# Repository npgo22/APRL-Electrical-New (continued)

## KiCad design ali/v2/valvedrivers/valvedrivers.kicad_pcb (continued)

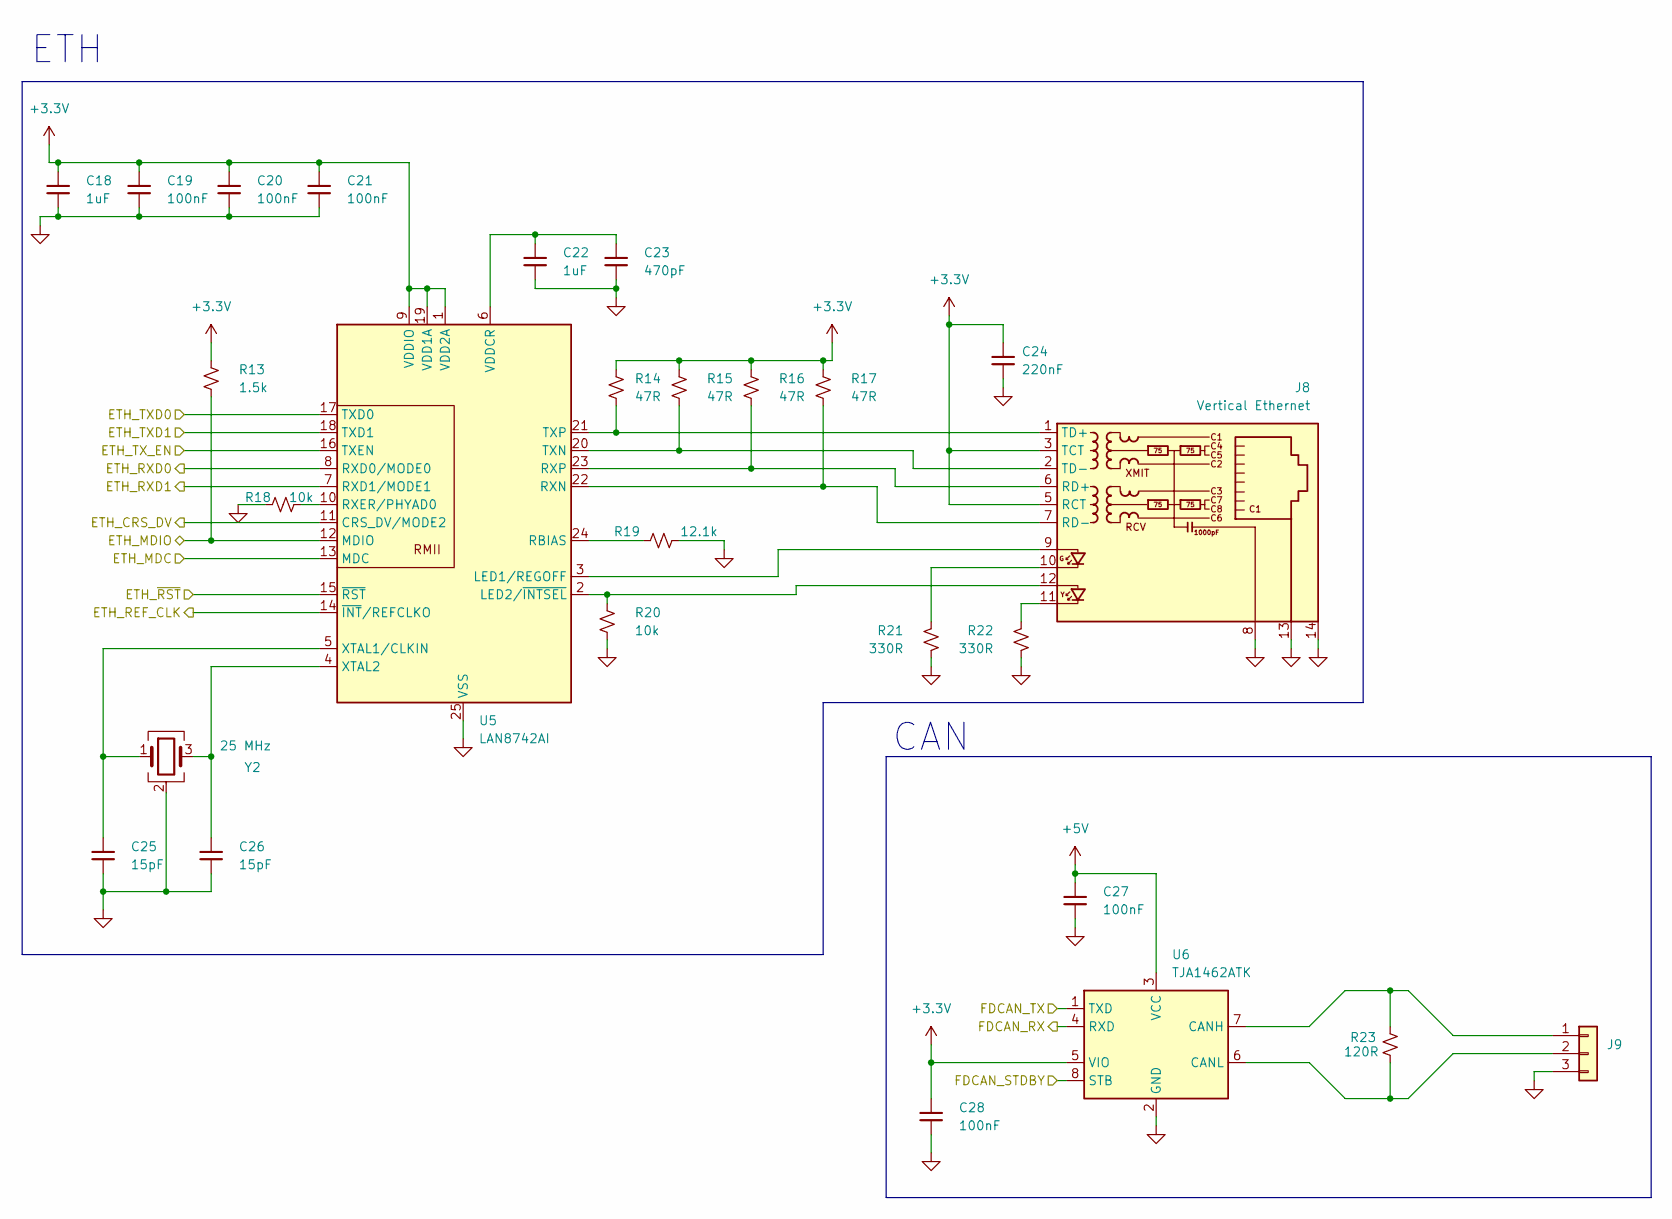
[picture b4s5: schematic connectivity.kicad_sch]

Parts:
C18, C22: 1uF; C_0603; MPN GRM188D72A105KE01
C19, C20, C21, C27, C28: 100nF; C_0603; MPN GRM188R72A104KA35
C23: 470pF; C_0603; MPN GRM1885C1H471JA01
C24: 220nF; C_0603; MPN GRM188R71H224KAC4
C25, C26: 15pF; C_0603; MPN GRM1885C2E150FW07
J8: Vertical Ethernet; RJ45_Hanrun_HY951180A_Vertical; MPN HY951180A
J9: Conn_01x03; Molex_CLIK-Mate_503159-0301_1x03-1MP_P1.50mm_Vertical; MPN 503159-0301
R13: 1.5k; R_0603; MPN RC0603FR-071K5L
R14, R15, R16, R17: 47R; R_0603; MPN RC0603FR-0747RL
R18, R20: 10k; R_0603; MPN RC0603FR-0710KL
R19: 12.1k; R_0603; MPN RT0603BRD0712K1L
R21, R22: 330R; R_0603; MPN RC0603FR-07330RL
R23: 120R; R_0603; MPN AC0603FR-07120RL
U5: LAN8742AI; VQFN-24-1EP_4x4mm_P0.5mm_EP2.5x2.5mm_ThermalVias; MPN LAN8742AI-CZ-TR
U6: TJA1462ATK; HVSON-8-1EP_3x3mm_P0.65mm_EP1.6x2.4mm_ThermalVias; MPN TJA1462ATK/0Z
Y2: 25 MHz; 3225-4P-L; MPN X1E0000210139

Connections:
+3.3V: C18.1, C19.1, C20.1, C21.1, C24.1, C28.1, J8.3 (TCT), J8.5 (RCT), R13.1, R14.1, R15.1, R16.1, R17.1, U5.1 (VDD2A), U5.9 (VDDIO), U5.19 (VDD1A), U6.5 (VIO); also elsewhere on the board
+5V: C27.1, U6.3 (VCC); also elsewhere on the board
/Connectivity/ETH_CRS_DV: U5.11 (CRS_DV/MODE2); also elsewhere on the board
/Connectivity/ETH_MDC: U5.13 (MDC); also elsewhere on the board
/Connectivity/ETH_MDIO: R13.2, U5.12 (MDIO); also elsewhere on the board
/Connectivity/ETH_REF_CLK: U5.14 (~INT/REFCLKO); also elsewhere on the board
/Connectivity/ETH_RXD0: U5.8 (RXD0/MODE0); also elsewhere on the board
/Connectivity/ETH_RXD1: U5.7 (RXD1/MODE1); also elsewhere on the board
/Connectivity/ETH_TXD0: U5.17 (TXD0); also elsewhere on the board
/Connectivity/ETH_TXD1: U5.18 (TXD1); also elsewhere on the board
/Connectivity/ETH_TX_EN: U5.16 (TXEN); also elsewhere on the board
/Connectivity/ETH_~RST: U5.15 (~RST); also elsewhere on the board
/Connectivity/FDCAN_RX: U6.4 (RXD); also elsewhere on the board
/Connectivity/FDCAN_STDBY: U6.8 (STB); also elsewhere on the board
/Connectivity/FDCAN_TX: U6.1 (TXD); also elsewhere on the board
GND: C18.2, C19.2, C20.2, C21.2, C22.2, C23.2, C24.2, C25.2, C26.2, C27.2, C28.2, J8.8, J8.13, J8.14, J9.3, R18.1, R19.2, R20.2, R21.2, R22.2, U5.25 (VSS), U6.2 (GND), U6.9 (GND), Y2.2 (G), Y2.4 (G); also elsewhere on the board
unnamed: J8.10, R21.1
unnamed: J8.11, R22.1
unnamed: J8.6 (RD+), R16.2, U5.23 (RXP)
unnamed: J8.7 (RD-), R17.2, U5.22 (RXN)
unnamed: J8.1 (TD+), R14.2, U5.21 (TXP)
unnamed: J8.2 (TD-), R15.2, U5.20 (TXN)
unnamed: J9.1, R23.2, U6.7 (CANH)
unnamed: J9.2, R23.1, U6.6 (CANL)
unnamed: J8.9, U5.3 (LED1/REGOFF)
unnamed: J8.12, R20.1, U5.2 (LED2/~INTSEL)
unnamed: R19.1, U5.24 (RBIAS)
unnamed: R18.2, U5.10 (RXER/PHYAD0)
unnamed: C22.1, C23.1, U5.6 (VDDCR)
unnamed: C25.1, U5.5 (XTAL1/CLKIN), Y2.1
unnamed: C26.1, U5.4 (XTAL2), Y2.3

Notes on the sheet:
ETH
CAN

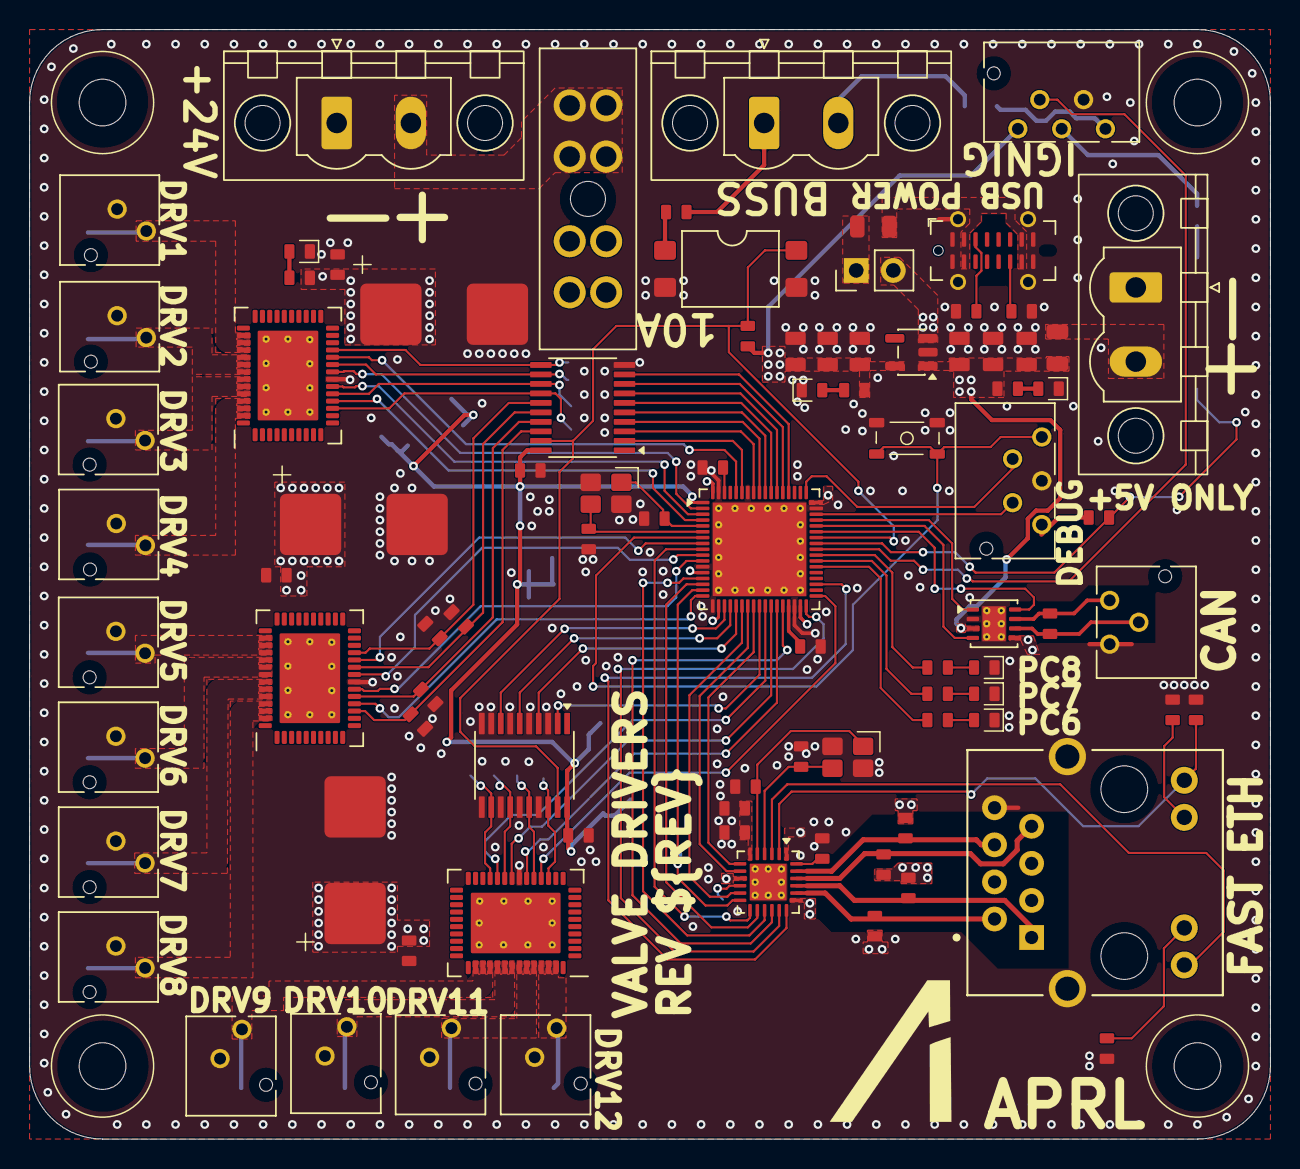
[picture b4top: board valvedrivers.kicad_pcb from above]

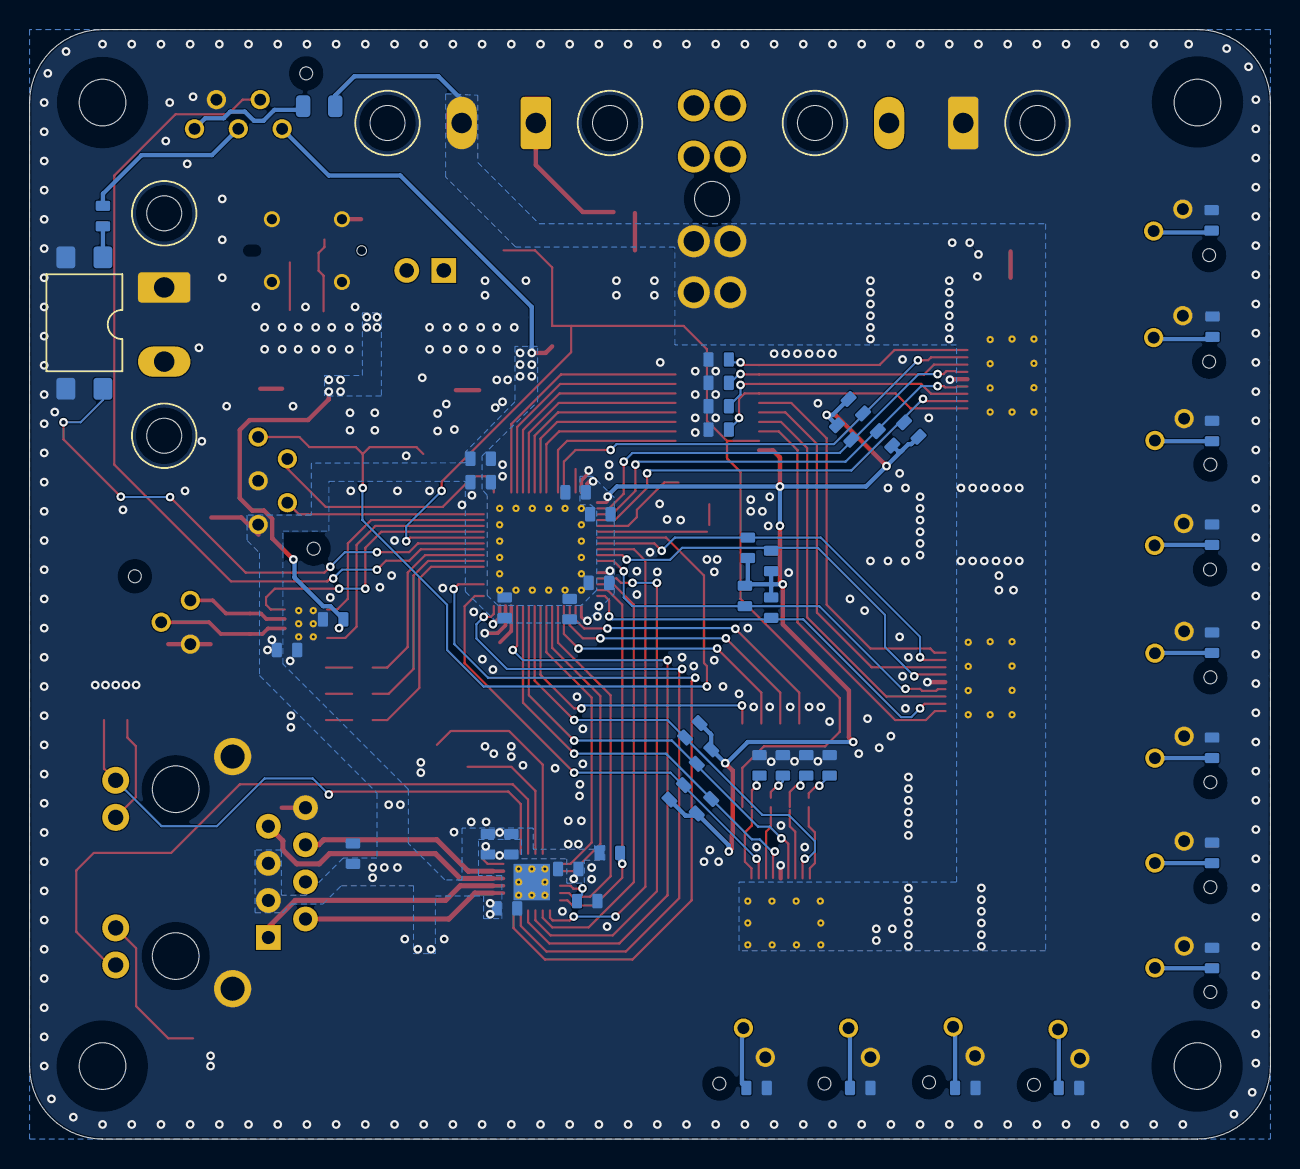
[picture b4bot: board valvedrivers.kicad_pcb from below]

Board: 4 copper layers, 85.0 x 76.0 mm, 144 parts (51 on the bottom side), 110 nets.

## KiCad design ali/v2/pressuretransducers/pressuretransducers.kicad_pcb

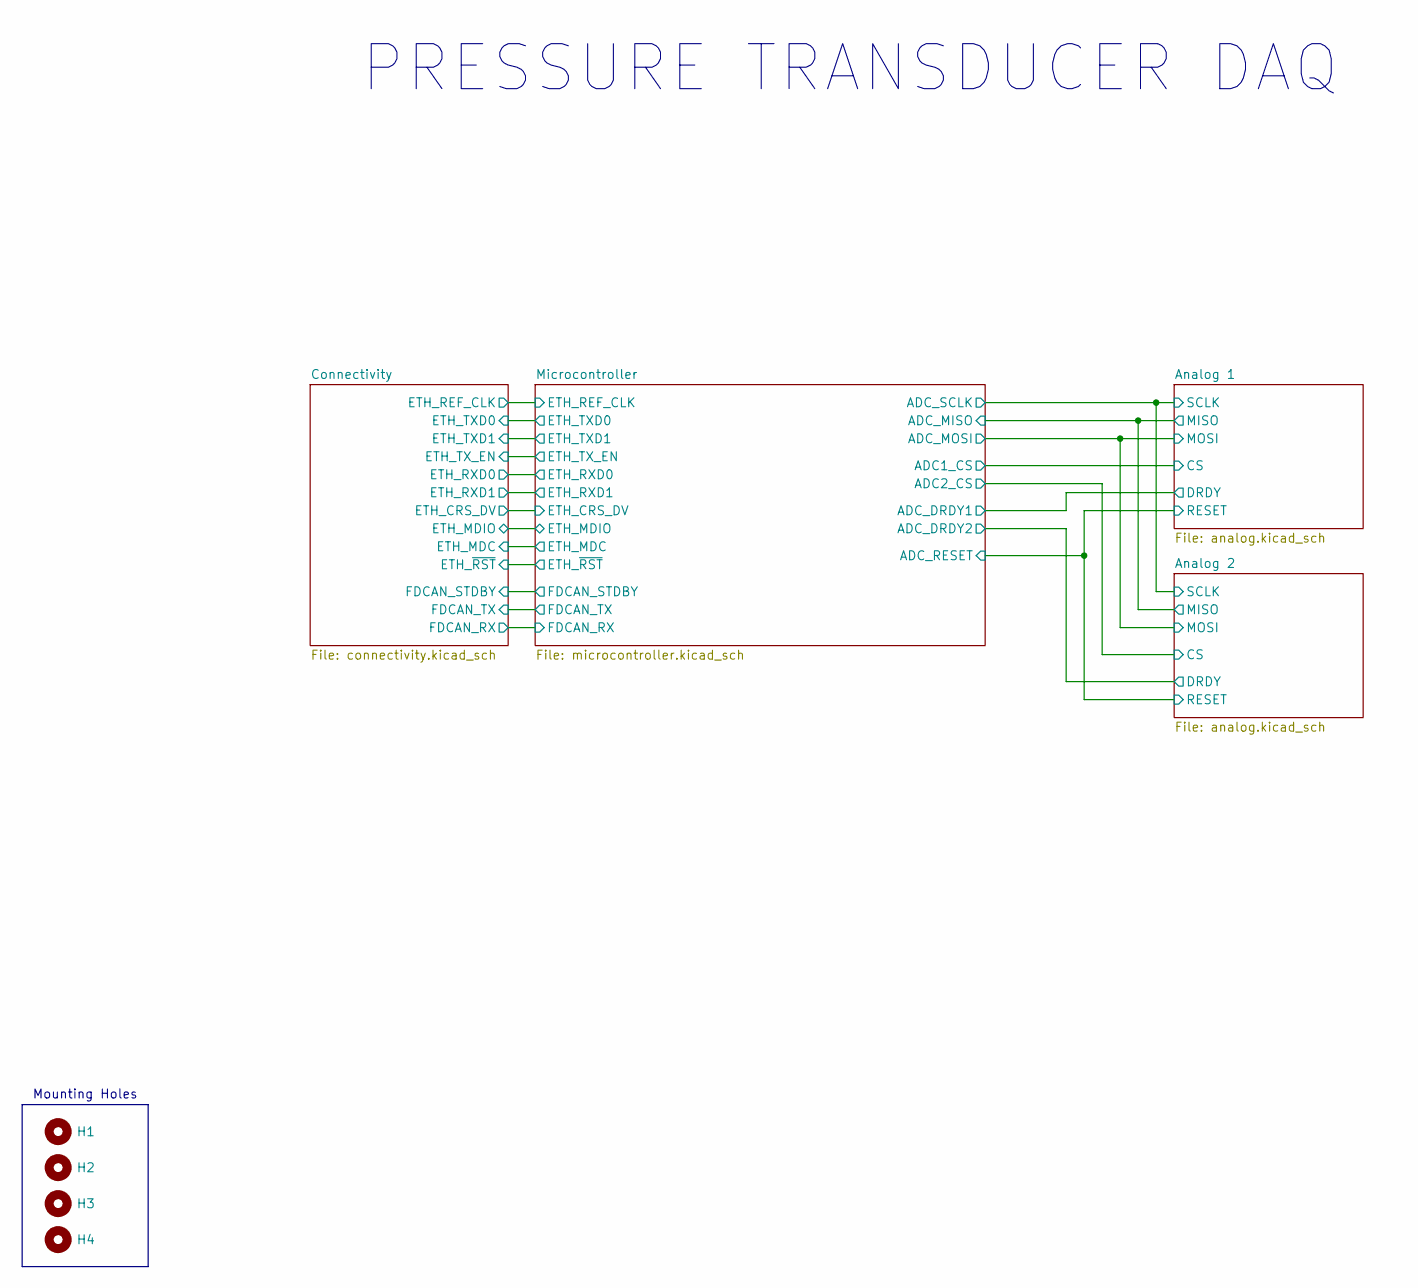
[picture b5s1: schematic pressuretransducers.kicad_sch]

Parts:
H1, H2, H3, H4: MountingHole; MountingHole_3.2mm_M3

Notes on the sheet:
PRESSURE TRANSDUCER DAQ
Mounting Holes

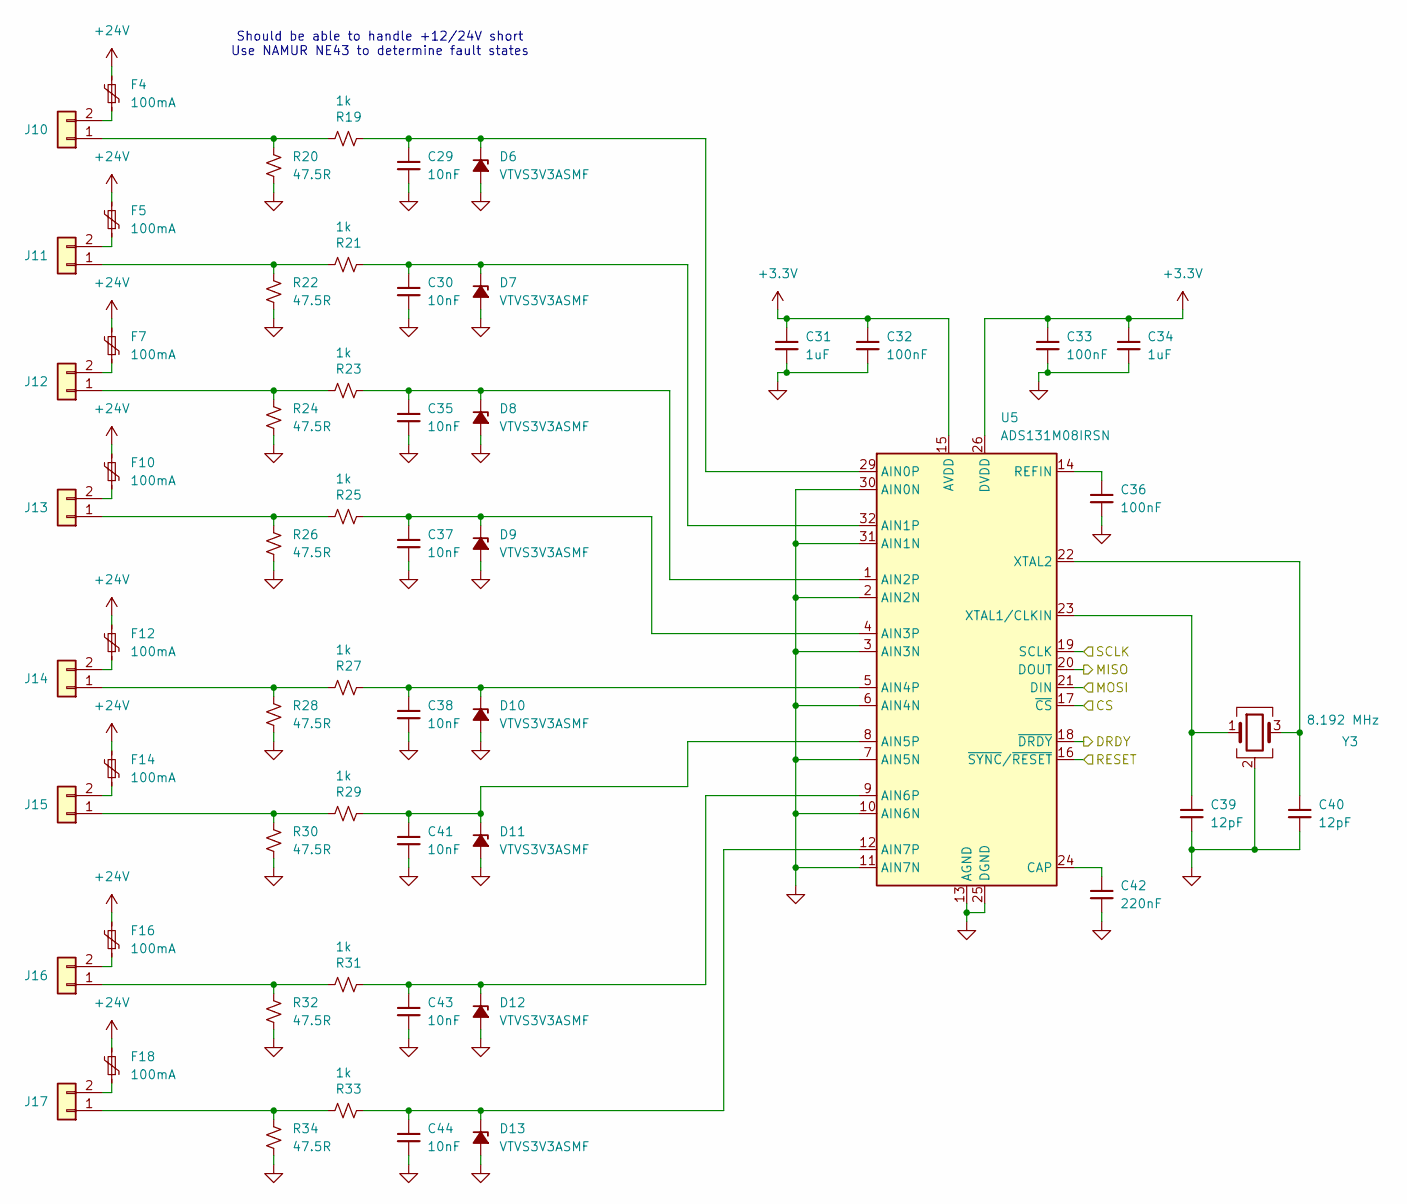
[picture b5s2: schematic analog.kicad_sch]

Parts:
C29, C30, C35, C37, C38, C41, C43, C44: 10nF; C_0603; MPN GRM1885C1H103JA01
C31, C34: 1uF; C_0603; MPN GRM188D72A105KE01
C32, C33, C36: 100nF; C_0603; MPN GRM188R72A104KA35
C39, C40: 12pF; C_0603; MPN C0603C120J5GACTU
C42: 220nF; C_0603; MPN GRM188R71H224KAC4
D6, D7, D8, D9, D10, D11, D12, D13: VTVS3V3ASMF; D_SMF; MPN VTVS3V3ASMF-M3-08
F4, F5, F7, F10, F12, F14, F16, F18: 100mA; Fuse_1206_3216Metric; MPN 1206L010/60WR
J10, J11, J12, J13, J14, J15, J16, J17: Conn_01x02; Molex_CLIK-Mate_503159-0201_1x02-1MP_P1.50mm_Vertical; MPN 503159-0201
R19, R21, R23, R25, R27, R29, R31, R33: 1k; R_0603; MPN RT0603BRD071KL
R20, R22, R24, R26, R28, R30, R32, R34: 47.5R; R_0805; MPN ERA-6AEB47R5V
U5: ADS131M08IRSN; QFN-32_EP_4.4x4.4_Pitch0.4mm; MPN ADS131M08IRSNR
Y3: 8.192 MHz; 3225-4P-L; MPN 7B008192I01

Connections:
+3.3V: C31.1, C32.1, C33.1, C34.1, U5.15 (AVDD), U5.26 (DVDD); also elsewhere on the board
+24V: F4.2, F5.2, F7.2, F10.2, F12.2, F14.2, F16.2, F18.2; also elsewhere on the board
/Analog 1/CS: U5.17 (~CS); also elsewhere on the board
/Analog 1/DRDY: U5.18 (~DRDY); also elsewhere on the board
/Analog 1/MISO: U5.20 (DOUT); also elsewhere on the board
/Analog 1/MOSI: U5.21 (DIN); also elsewhere on the board
/Analog 1/RESET: U5.16 (~SYNC/~RESET); also elsewhere on the board
/Analog 1/SCLK: U5.19 (SCLK); also elsewhere on the board
GND: C29.1, C30.1, C31.2, C32.2, C33.2, C34.2, C35.1, C36.2, C37.1, C38.1, C39.2, C40.2, C41.1, C42.2, C43.1, C44.1, D6.2 (A), D7.2 (A), D8.2 (A), D9.2 (A), D10.2 (A), D11.2 (A), D12.2 (A), D13.2 (A), R20.2, R22.2, R24.2, R26.2, R28.2, R30.2, R32.2, R34.2, U5.2 (AIN2N), U5.3 (AIN3N), U5.6 (AIN4N), U5.7 (AIN5N), U5.10 (AIN6N), U5.11 (AIN7N), U5.13 (AGND), U5.25 (DGND), U5.27 (AGND), U5.28 (AGND), U5.30 (AIN0N), U5.31 (AIN1N), U5.33 (GND), Y3.2 (G), Y3.4 (G); also elsewhere on the board
unnamed: C29.2, D6.1 (K), R19.2, U5.29 (AIN0P)
unnamed: C30.2, D7.1 (K), R21.2, U5.32 (AIN1P)
unnamed: C35.2, D8.1 (K), R23.2, U5.1 (AIN2P)
unnamed: C37.2, D9.1 (K), R25.2, U5.4 (AIN3P)
unnamed: C38.2, D10.1 (K), R27.2, U5.5 (AIN4P)
unnamed: C41.2, D11.1 (K), R29.2, U5.8 (AIN5P)
unnamed: C43.2, D12.1 (K), R31.2, U5.9 (AIN6P)
unnamed: C44.2, D13.1 (K), R33.2, U5.12 (AIN7P)
unnamed: J10.1, R19.1, R20.1
unnamed: F4.1, J10.2
unnamed: J11.1, R21.1, R22.1
unnamed: F5.1, J11.2
unnamed: J12.1, R23.1, R24.1
unnamed: F7.1, J12.2
unnamed: J13.1, R25.1, R26.1
unnamed: F10.1, J13.2
unnamed: J14.1, R27.1, R28.1
unnamed: F12.1, J14.2
unnamed: J15.1, R29.1, R30.1
unnamed: F14.1, J15.2
unnamed: J16.1, R31.1, R32.1
unnamed: F16.1, J16.2
unnamed: J17.1, R33.1, R34.1
unnamed: F18.1, J17.2
unnamed: C42.1, U5.24 (CAP)
unnamed: C36.1, U5.14 (REFIN)
unnamed: C39.1, U5.23 (XTAL1/CLKIN), Y3.1
unnamed: C40.1, U5.22 (XTAL2), Y3.3

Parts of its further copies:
C45, C46, C51, C53, C54, C57, C59, C60: 10nF; C_0603; MPN GRM1885C1H103JA01
C47, C50: 1uF; C_0603; MPN GRM188D72A105KE01
C48, C49, C52: 100nF; C_0603; MPN GRM188R72A104KA35
C55, C56: 12pF; C_0603; MPN C0603C120J5GACTU
C58: 220nF; C_0603; MPN GRM188R71H224KAC4
D14, D15, D16, D17, D18, D19, D20, D21: VTVS3V3ASMF; D_SMF; MPN VTVS3V3ASMF-M3-08
F6, F8, F9, F11, F13, F15, F17, F19: 100mA; Fuse_1206_3216Metric; MPN 1206L010/60WR
J18, J19, J20, J21, J22, J23, J24, J25: Conn_01x02; Molex_CLIK-Mate_503159-0201_1x02-1MP_P1.50mm_Vertical; MPN 503159-0201
R35, R37, R39, R41, R43, R45, R47, R49: 1k; R_0603; MPN RT0603BRD071KL
R36, R38, R40, R42, R44, R46, R48, R50: 47.5R; R_0805; MPN ERA-6AEB47R5V
U6: ADS131M08IRSN; QFN-32_EP_4.4x4.4_Pitch0.4mm; MPN ADS131M08IRSNR
Y4: 8.192 MHz; 3225-4P-L; MPN 7B008192I01

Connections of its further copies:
+3.3V: C47.1, C48.1, C49.1, C50.1, U6.15 (AVDD), U6.26 (DVDD); also elsewhere on the board
+24V: F6.2, F8.2, F9.2, F11.2, F13.2, F15.2, F17.2, F19.2; also elsewhere on the board
/Analog 1/MISO: U6.20 (DOUT); also elsewhere on the board
/Analog 1/MOSI: U6.21 (DIN); also elsewhere on the board
/Analog 1/RESET: U6.16 (~SYNC/~RESET); also elsewhere on the board
/Analog 1/SCLK: U6.19 (SCLK); also elsewhere on the board
/Analog 2/CS: U6.17 (~CS); also elsewhere on the board
/Analog 2/DRDY: U6.18 (~DRDY); also elsewhere on the board
GND: C45.1, C46.1, C47.2, C48.2, C49.2, C50.2, C51.1, C52.2, C53.1, C54.1, C55.2, C56.2, C57.1, C58.2, C59.1, C60.1, D14.2 (A), D15.2 (A), D16.2 (A), D17.2 (A), D18.2 (A), D19.2 (A), D20.2 (A), D21.2 (A), R36.2, R38.2, R40.2, R42.2, R44.2, R46.2, R48.2, R50.2, U6.2 (AIN2N), U6.3 (AIN3N), U6.6 (AIN4N), U6.7 (AIN5N), U6.10 (AIN6N), U6.11 (AIN7N), U6.13 (AGND), U6.25 (DGND), U6.27 (AGND), U6.28 (AGND), U6.30 (AIN0N), U6.31 (AIN1N), U6.33 (GND), Y4.2 (G), Y4.4 (G); also elsewhere on the board
unnamed: C45.2, D14.1 (K), R35.2, U6.29 (AIN0P)
unnamed: C46.2, D15.1 (K), R37.2, U6.32 (AIN1P)
unnamed: C51.2, D16.1 (K), R39.2, U6.1 (AIN2P)
unnamed: C53.2, D17.1 (K), R41.2, U6.4 (AIN3P)
unnamed: C54.2, D18.1 (K), R43.2, U6.5 (AIN4P)
unnamed: C57.2, D19.1 (K), R45.2, U6.8 (AIN5P)
unnamed: C59.2, D20.1 (K), R47.2, U6.9 (AIN6P)
unnamed: C60.2, D21.1 (K), R49.2, U6.12 (AIN7P)
unnamed: J18.1, R35.1, R36.1
unnamed: F8.1, J18.2
unnamed: J19.1, R37.1, R38.1
unnamed: F6.1, J19.2
unnamed: J20.1, R39.1, R40.1
unnamed: F9.1, J20.2
unnamed: J21.1, R41.1, R42.1
unnamed: F11.1, J21.2
unnamed: J22.1, R43.1, R44.1
unnamed: F13.1, J22.2
unnamed: J23.1, R45.1, R46.1
unnamed: F15.1, J23.2
unnamed: J24.1, R47.1, R48.1
unnamed: F17.1, J24.2
unnamed: J25.1, R49.1, R50.1
unnamed: F19.1, J25.2
unnamed: C58.1, U6.24 (CAP)
unnamed: C52.1, U6.14 (REFIN)
unnamed: C55.1, U6.23 (XTAL1/CLKIN), Y4.1
unnamed: C56.1, U6.22 (XTAL2), Y4.3

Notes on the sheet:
Should be able to handle +12/24V short Use NAMUR NE43 to determine fault states

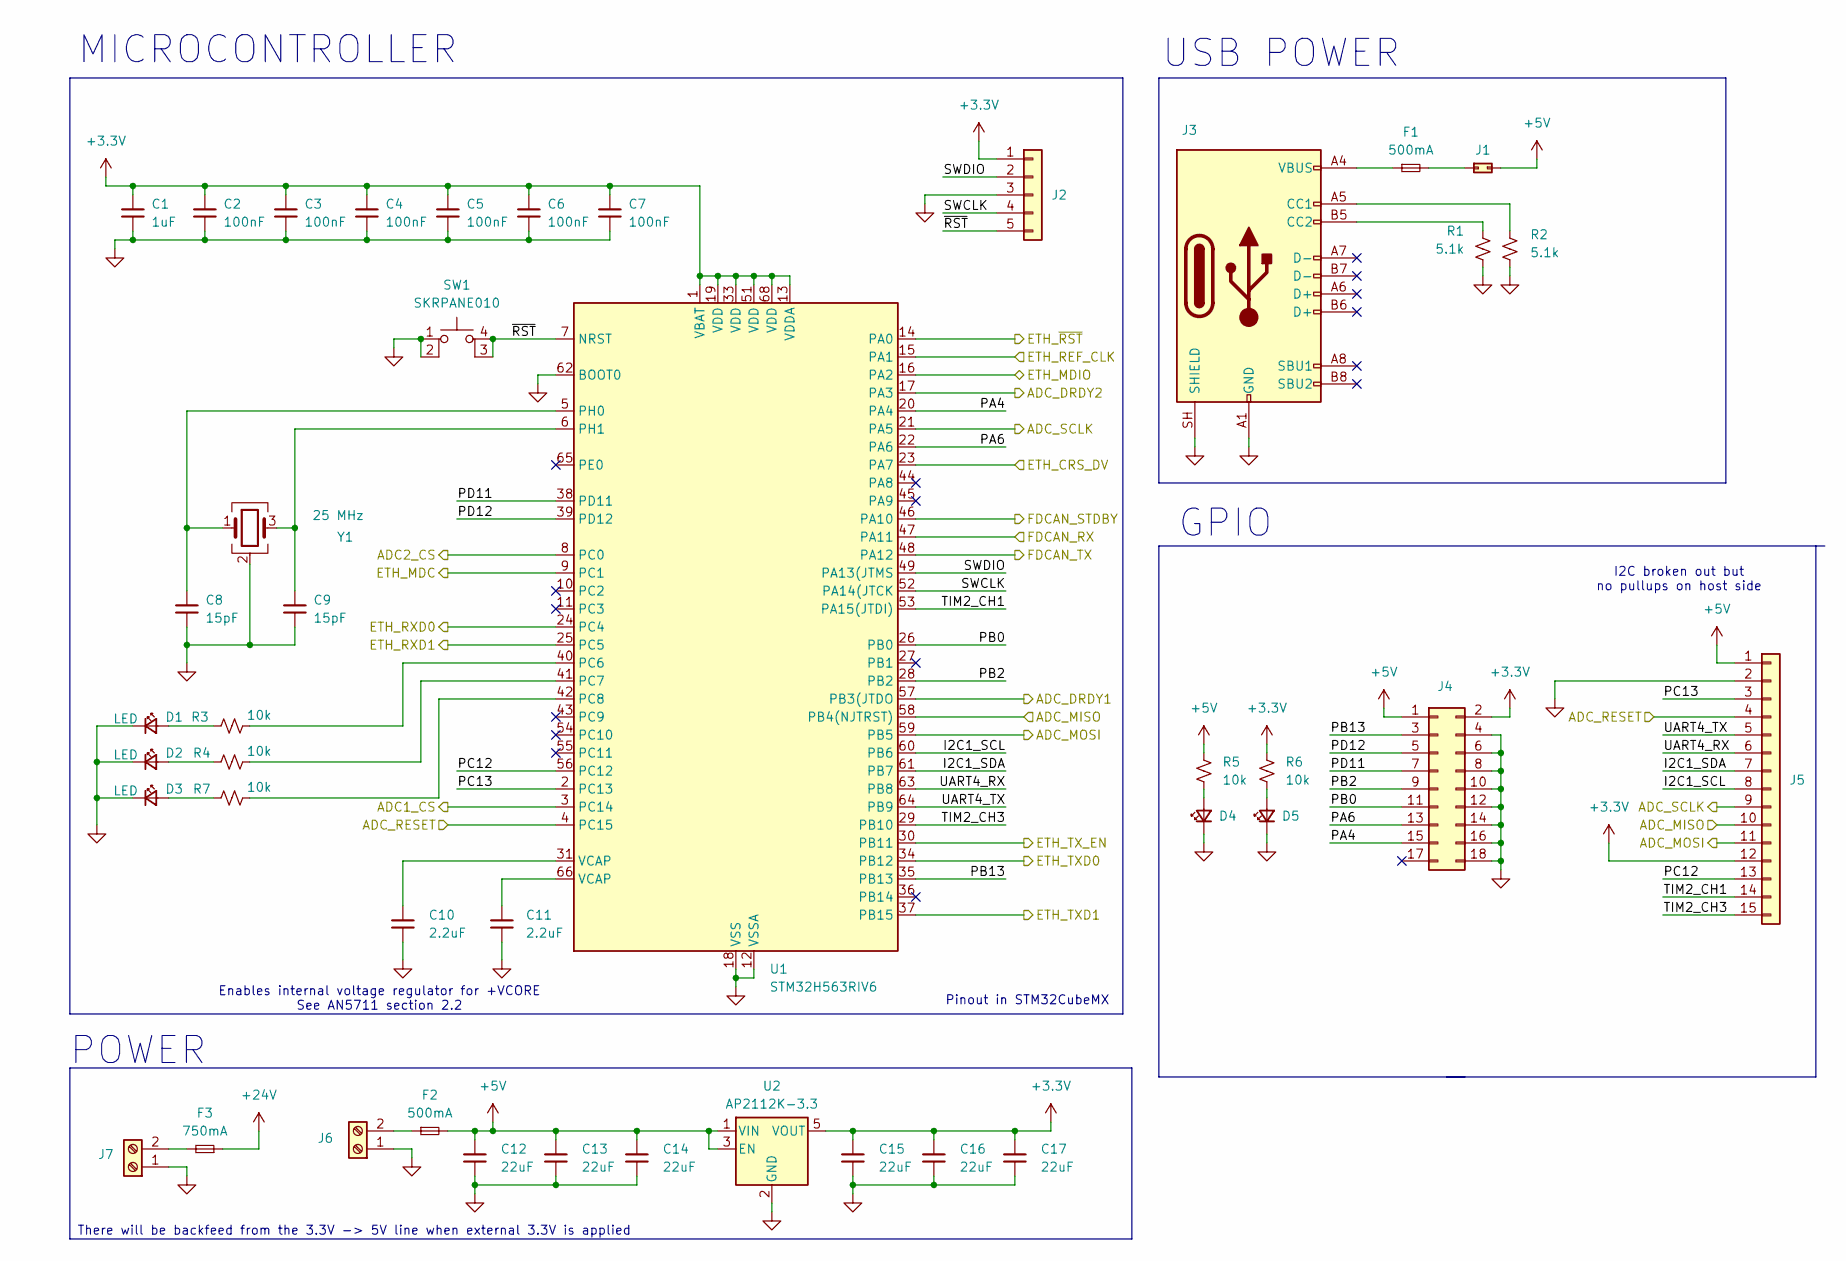
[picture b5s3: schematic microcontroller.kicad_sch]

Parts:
C1: 1uF; C_0603; MPN GRM188D72A105KE01
C2, C3, C4, C5, C6, C7: 100nF; C_0603; MPN GRM188R72A104KA35
C8, C9: 15pF; C_0603; MPN GRM1885C2E150FW07
C10, C11: 2.2uF; C_0603; MPN GRM188R71A225KE15
C12, C13, C14, C15, C16, C17: 22uF; C_0805; MPN GRM21BZ71A226ME15
D1, D2, D3, D4, D5: LED; LED_0603
F1, F2: 500mA; Fuse_0805_2012Metric; MPN 0805L050WR
F3: 750mA; Fuse_1812_4532Metric; MPN 1812L075/33DR
J1: Conn_02x01; PinHeader_1x02_P2.54mm_Vertical
J2: Conn_01x05; Molex_CLIK-Mate_503159-0501_1x05-1MP_P1.50mm_Vertical; MPN 503159-0501
J3: USB_C_Receptacle_USB2.0_16P; USB_C_Receptacle_G-Switch_GT-USB-7051x; MPN GT-USB-7051A
J4: Conn_02x09_Counter_Clockwise; IDC-Header_2x09_P2.54mm_Vertical; MPN XDFH-0254-2*9P
J5: Conn_01x15; Molex_CLIK-Mate_503159-1501_1x15-1MP_P1.50mm_Vertical; MPN 503159-1501
J6, J7: Screw_Terminal_01x02; PhoenixContact_MSTBV_2,5_2-GF-5,08_1x02_P5.08mm_Vertical_Th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; MPN MSTBV 2,5/ 2-GF-5,08
R1, R2: 5.1k; R_0603; MPN AC0603FR-075K1L
R3, R4, R5, R6, R7: 10k; R_0603; MPN AC0603FR-0710KL
SW1: SKRPANE010; MPN SKRPANE010
U1: STM32H563RIV6; QFN-68-1EP_8x8mm_P0.4mm_EP6.4x6.4mm; MPN STM32H563RIV6
U2: AP2112K-3.3; SOT-23-5; MPN AP2112K-3.3TRG1
Y1: 25 MHz; 3225-4P-L; MPN X1E0000210139

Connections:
+3.3V: C1.1, C2.1, C3.1, C4.1, C5.1, C6.1, C7.1, C15.1, C16.1, C17.1, J2.1, J4.2, J5.12, R6.1, U1.1 (VBAT), U1.13 (VDDA), U1.19 (VDD), U1.33 (VDD), U1.51 (VDD), U1.68 (VDD), U2.5 (VOUT); also elsewhere on the board
+5V: C12.1, C13.1, C14.1, F2.2, J1.2, J4.1, J5.1, R5.1, U2.1 (VIN), U2.3 (EN); also elsewhere on the board
+24V: F3.1; also elsewhere on the board
/Analog 1/CS: U1.3 (PC14); also elsewhere on the board
/Analog 1/DRDY: U1.57 (PB3(JTDO); also elsewhere on the board
/Analog 1/MISO: J5.10, U1.58 (PB4(NJTRST)); also elsewhere on the board
/Analog 1/MOSI: J5.11, U1.59 (PB5); also elsewhere on the board
/Analog 1/RESET: J5.4, U1.4 (PC15); also elsewhere on the board
/Analog 1/SCLK: J5.9, U1.21 (PA5); also elsewhere on the board
/Analog 2/CS: U1.8 (PC0); also elsewhere on the board
/Analog 2/DRDY: U1.17 (PA3); also elsewhere on the board
/Connectivity/ETH_CRS_DV: U1.23 (PA7); also elsewhere on the board
/Connectivity/ETH_MDC: U1.9 (PC1); also elsewhere on the board
/Connectivity/ETH_MDIO: U1.16 (PA2); also elsewhere on the board
/Connectivity/ETH_REF_CLK: U1.15 (PA1); also elsewhere on the board
/Connectivity/ETH_RXD0: U1.24 (PC4); also elsewhere on the board
/Connectivity/ETH_RXD1: U1.25 (PC5); also elsewhere on the board
/Connectivity/ETH_TXD0: U1.34 (PB12); also elsewhere on the board
/Connectivity/ETH_TXD1: U1.37 (PB15); also elsewhere on the board
/Connectivity/ETH_TX_EN: U1.30 (PB11); also elsewhere on the board
/Connectivity/ETH_~RST: U1.14 (PA0); also elsewhere on the board
/Connectivity/FDCAN_RX: U1.47 (PA11); also elsewhere on the board
/Connectivity/FDCAN_STDBY: U1.46 (PA10); also elsewhere on the board
/Connectivity/FDCAN_TX: U1.48 (PA12); also elsewhere on the board
/Microcontroller/I2C1_SCL: J5.8, U1.60 (PB6)
/Microcontroller/I2C1_SDA: J5.7, U1.61 (PB7)
/Microcontroller/PA4: J4.15, U1.20 (PA4)
/Microcontroller/PA6: J4.13, U1.22 (PA6)
/Microcontroller/PB0: J4.11, U1.26 (PB0)
/Microcontroller/PB2: J4.9, U1.28 (PB2)
/Microcontroller/PB13: J4.3, U1.35 (PB13)
/Microcontroller/PC12: J5.13, U1.56 (PC12)
/Microcontroller/PC13: J5.3, U1.2 (PC13)
/Microcontroller/PD11: J4.7, U1.38 (PD11)
/Microcontroller/PD12: J4.5, U1.39 (PD12)
/Microcontroller/SWCLK: J2.4, U1.52 (PA14(JTCK)
/Microcontroller/SWDIO: J2.2, U1.49 (PA13(JTMS)
/Microcontroller/TIM2_CH1: J5.14, U1.53 (PA15(JTDI))
/Microcontroller/TIM2_CH3: J5.15, U1.29 (PB10)
/Microcontroller/UART4_RX: J5.6, U1.63 (PB8)
/Microcontroller/UART4_TX: J5.5, U1.64 (PB9)
/Microcontroller/~RST: J2.5, SW1.3 (K), SW1.4 (A), U1.7 (NRST)
GND: C1.2, C2.2, C3.2, C4.2, C5.2, C6.2, C7.2, C8.2, C9.2, C10.2, C11.2, C12.2, C13.2, C14.2, C15.2, C16.2, C17.2, D1.1 (K), D2.1 (K), D3.1 (K), D4.1 (K), D5.1 (K), J2.3, J3.A1 (GND), J3.A12 (GND), J3.B1 (GND), J3.B12 (GND), J3.SH (SHIELD), J4.4, J4.6, J4.8, J4.10, J4.12, J4.14, J4.16, J4.18, J5.2, J6.1, J7.1, R1.1, R2.2, SW1.1, SW1.2, U1.12 (VSSA), U1.18 (VSS), U1.32 (VSS), U1.50 (VSS), U1.62 (BOOT0), U1.67 (VSS), U1.69 (VSS), U2.2 (GND), Y1.2 (G), Y1.4 (G); also elsewhere on the board
unnamed: C10.1, U1.31 (VCAP)
unnamed: C11.1, U1.66 (VCAP)
unnamed: D1.2 (A), R3.1
unnamed: D2.2 (A), R4.1
unnamed: D3.2 (A), R7.1
unnamed: D4.2 (A), R5.2
unnamed: D5.2 (A), R6.2
unnamed: F1.1, J3.A4 (VBUS), J3.A9 (VBUS), J3.B4 (VBUS), J3.B9 (VBUS)
unnamed: F1.2, J1.1
unnamed: J3.A5 (CC1), R2.1
unnamed: J3.B5 (CC2), R1.2
unnamed: F2.1, J6.2
unnamed: F3.2, J7.2
unnamed: R3.2, U1.40 (PC6)
unnamed: R4.2, U1.41 (PC7)
unnamed: R7.2, U1.42 (PC8)
unnamed: C8.1, U1.5 (PH0), Y1.1
unnamed: C9.1, U1.6 (PH1), Y1.3

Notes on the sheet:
Enables internal voltage regulator for +VCORE See AN5711 section 2.2
POWER
MICROCONTROLLER
There will be backfeed from the 3.3V -> 5V line when external 3.3V is applied
USB POWER
I2C broken out but no pullups on host side
Pinout in STM32CubeMX
GPIO

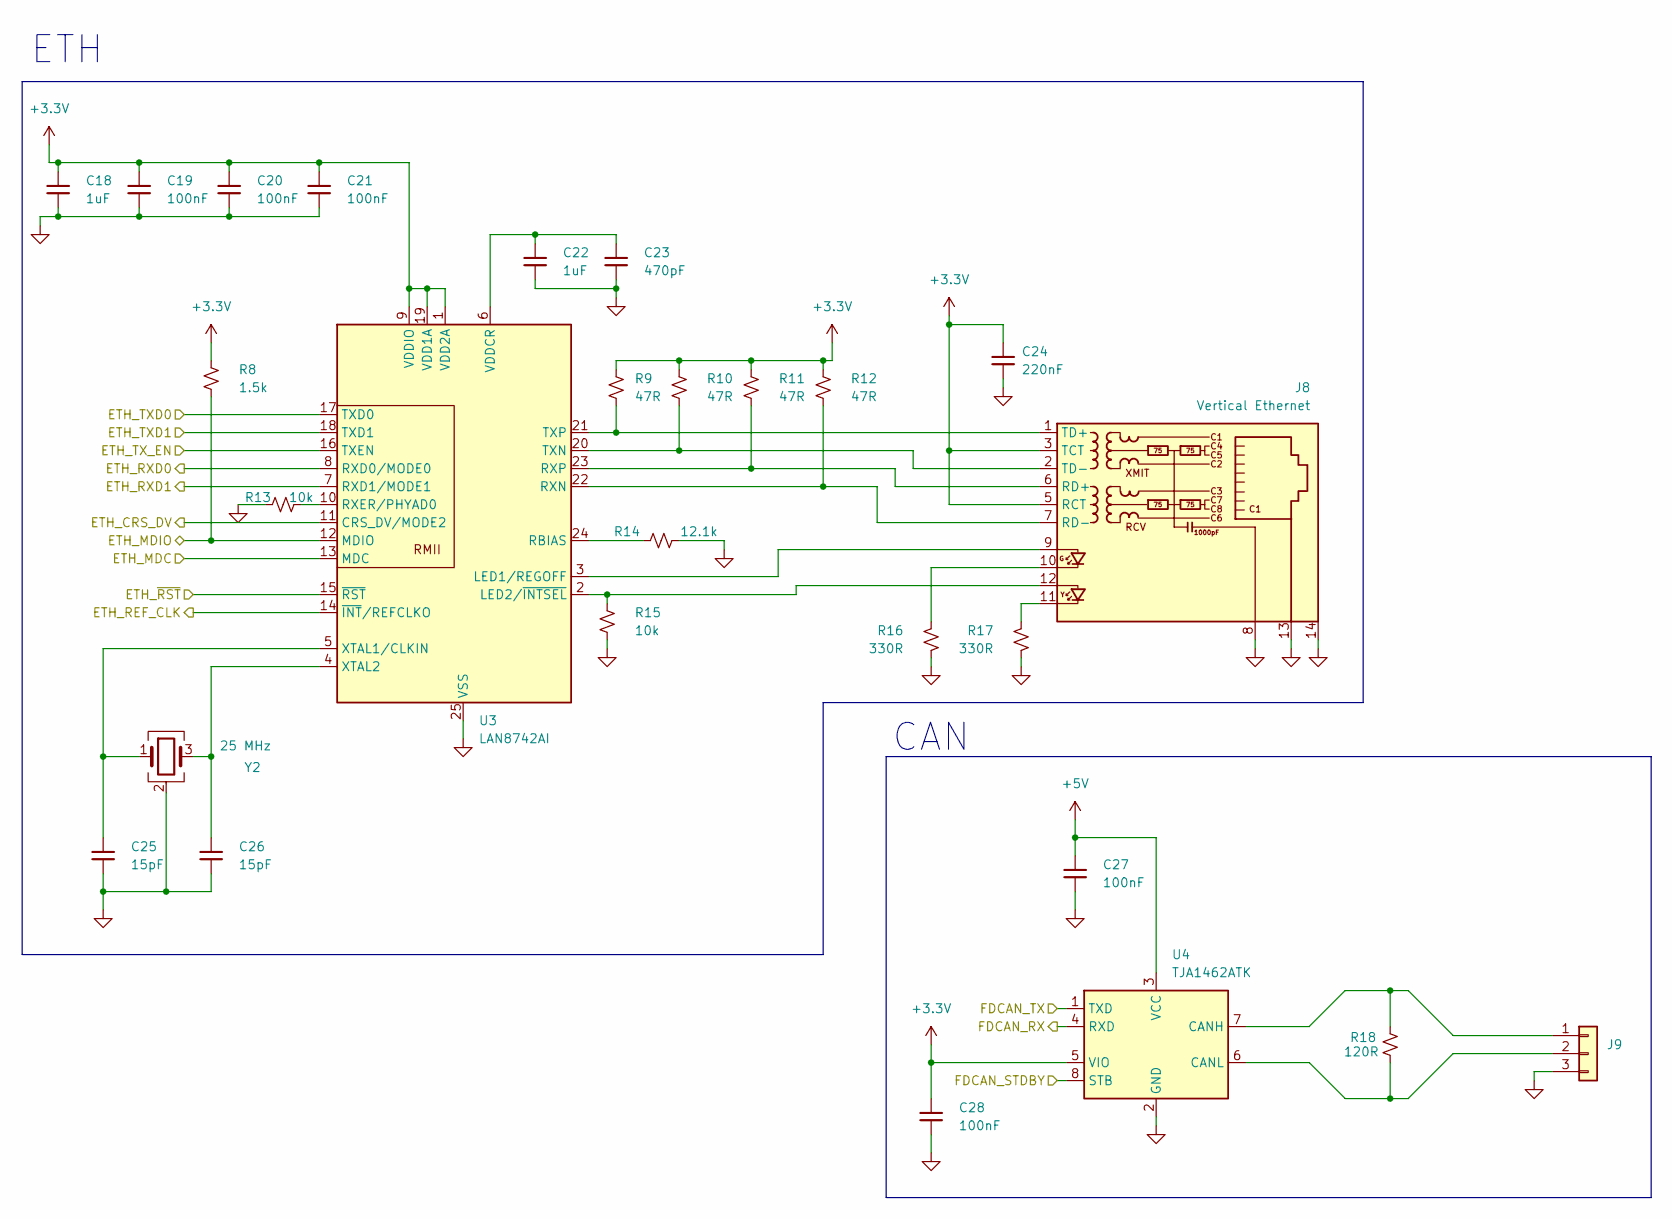
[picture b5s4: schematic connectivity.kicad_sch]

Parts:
C18, C22: 1uF; C_0603; MPN GRM188D72A105KE01
C19, C20, C21, C27, C28: 100nF; C_0603; MPN GRM188R72A104KA35
C23: 470pF; C_0603; MPN GRM1885C1H471JA01
C24: 220nF; C_0603; MPN GRM188R71H224KAC4
C25, C26: 15pF; C_0603; MPN GRM1885C2E150FW07
J8: Vertical Ethernet; RJ45_Hanrun_HY951180A_Vertical; MPN HY951180A
J9: Conn_01x03; Molex_CLIK-Mate_503159-0301_1x03-1MP_P1.50mm_Vertical; MPN 503159-0301
R8: 1.5k; R_0603; MPN RC0603FR-071K5L
R9, R10, R11, R12: 47R; R_0603; MPN RC0603FR-0747RL
R13, R15: 10k; R_0603; MPN RC0603FR-0710KL
R14: 12.1k; R_0603; MPN RT0603BRD0712K1L
R16, R17: 330R; R_0603; MPN RC0603FR-07330RL
R18: 120R; R_0603; MPN AC0603FR-07120RL
U3: LAN8742AI; VQFN-24-1EP_4x4mm_P0.5mm_EP2.5x2.5mm_ThermalVias; MPN LAN8742AI-CZ-TR
U4: TJA1462ATK; HVSON-8-1EP_3x3mm_P0.65mm_EP1.6x2.4mm_ThermalVias; MPN TJA1462ATK/0Z
Y2: 25 MHz; 3225-4P-L; MPN X1E0000210139

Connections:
+3.3V: C18.1, C19.1, C20.1, C21.1, C24.1, C28.1, J8.3 (TCT), J8.5 (RCT), R8.1, R9.1, R10.1, R11.1, R12.1, U3.1 (VDD2A), U3.9 (VDDIO), U3.19 (VDD1A), U4.5 (VIO); also elsewhere on the board
+5V: C27.1, U4.3 (VCC); also elsewhere on the board
/Connectivity/ETH_CRS_DV: U3.11 (CRS_DV/MODE2); also elsewhere on the board
/Connectivity/ETH_MDC: U3.13 (MDC); also elsewhere on the board
/Connectivity/ETH_MDIO: R8.2, U3.12 (MDIO); also elsewhere on the board
/Connectivity/ETH_REF_CLK: U3.14 (~INT/REFCLKO); also elsewhere on the board
/Connectivity/ETH_RXD0: U3.8 (RXD0/MODE0); also elsewhere on the board
/Connectivity/ETH_RXD1: U3.7 (RXD1/MODE1); also elsewhere on the board
/Connectivity/ETH_TXD0: U3.17 (TXD0); also elsewhere on the board
/Connectivity/ETH_TXD1: U3.18 (TXD1); also elsewhere on the board
/Connectivity/ETH_TX_EN: U3.16 (TXEN); also elsewhere on the board
/Connectivity/ETH_~RST: U3.15 (~RST); also elsewhere on the board
/Connectivity/FDCAN_RX: U4.4 (RXD); also elsewhere on the board
/Connectivity/FDCAN_STDBY: U4.8 (STB); also elsewhere on the board
/Connectivity/FDCAN_TX: U4.1 (TXD); also elsewhere on the board
GND: C18.2, C19.2, C20.2, C21.2, C22.2, C23.2, C24.2, C25.2, C26.2, C27.2, C28.2, J8.8, J8.13, J8.14, J9.3, R13.1, R14.2, R15.2, R16.2, R17.2, U3.25 (VSS), U4.2 (GND), U4.9 (GND), Y2.2 (G), Y2.4 (G); also elsewhere on the board
unnamed: J8.10, R16.1
unnamed: J8.11, R17.1
unnamed: J8.6 (RD+), R11.2, U3.23 (RXP)
unnamed: J8.7 (RD-), R12.2, U3.22 (RXN)
unnamed: J8.1 (TD+), R9.2, U3.21 (TXP)
unnamed: J8.2 (TD-), R10.2, U3.20 (TXN)
unnamed: J9.1, R18.2, U4.7 (CANH)
unnamed: J9.2, R18.1, U4.6 (CANL)
unnamed: J8.9, U3.3 (LED1/REGOFF)
unnamed: J8.12, R15.1, U3.2 (LED2/~INTSEL)
unnamed: R14.1, U3.24 (RBIAS)
unnamed: R13.2, U3.10 (RXER/PHYAD0)
unnamed: C22.1, C23.1, U3.6 (VDDCR)
unnamed: C25.1, U3.5 (XTAL1/CLKIN), Y2.1
unnamed: C26.1, U3.4 (XTAL2), Y2.3

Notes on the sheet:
CAN
ETH
